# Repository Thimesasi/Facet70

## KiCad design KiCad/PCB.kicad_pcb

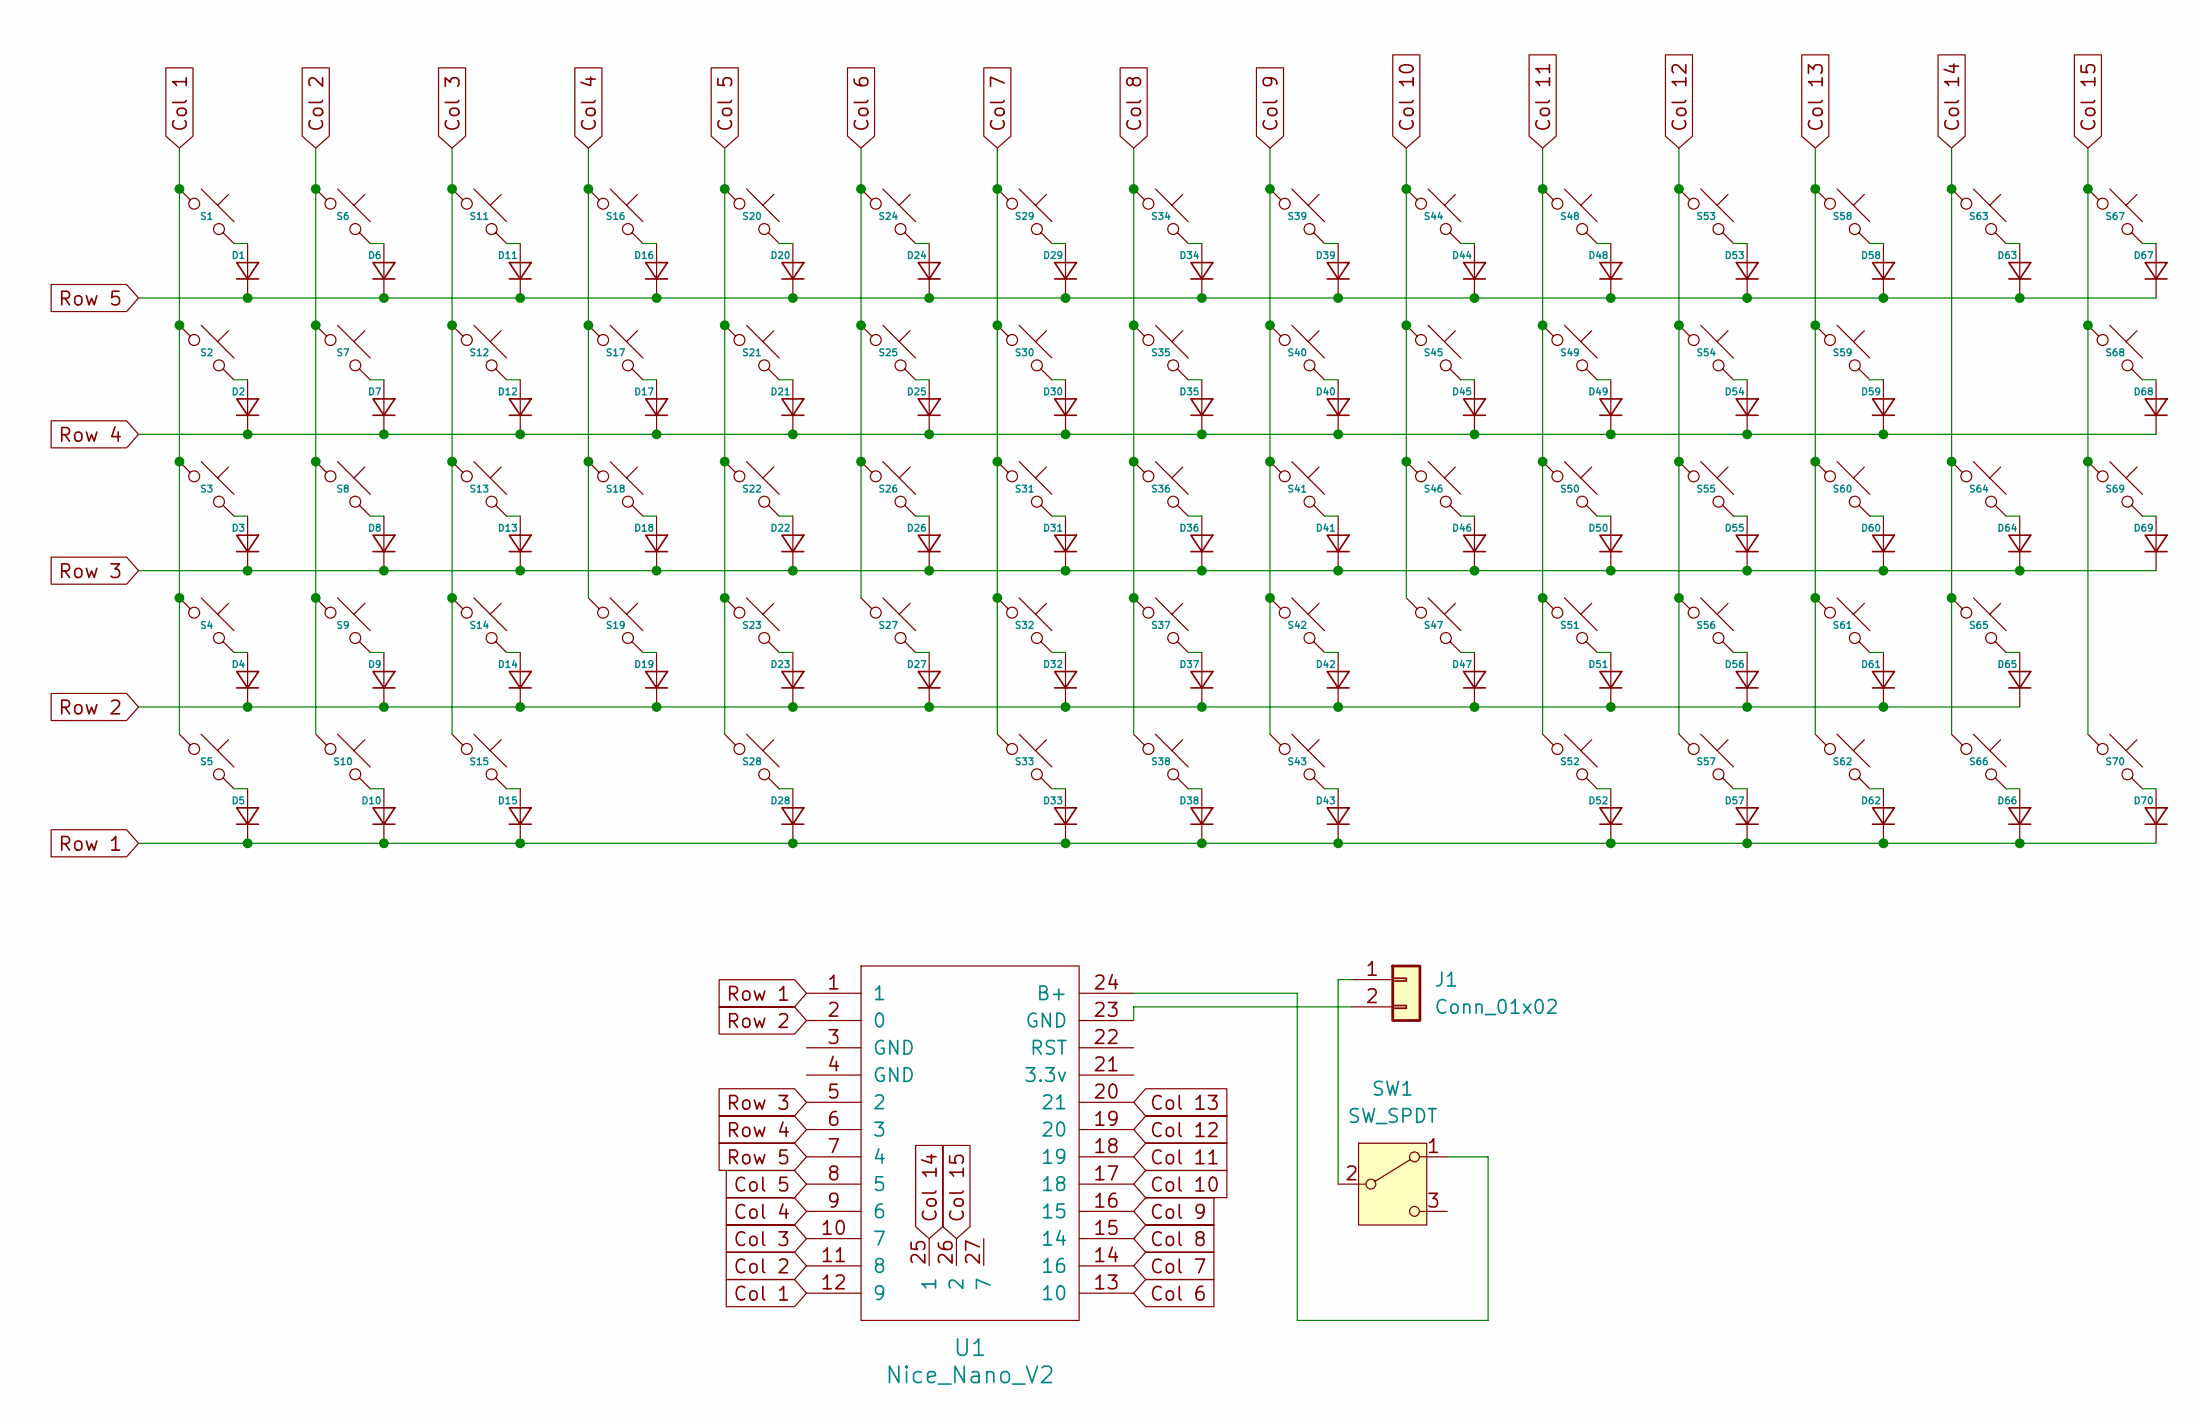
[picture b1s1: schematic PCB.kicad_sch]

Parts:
D1, D2, D3, D4, D5, D6, D7, D8, D9, D10, D11, D12, D13, D14, D15, D16, D17, D18, D19, D20, D21, D22, D23, D24, D25, D26, D27, D28, D29, D30, D31, D32, D33, D34, D35, D36, D37, D38, D39, D40, D41, D42, D43, D44, D45, D46, D47, D48, D49, D50, D51, D52, D53, D54, D55, D56, D57, D58, D59, D60, D61, D62, D63, D64, D65, D66, D67, D68, D69, D70: Diode_SOD-123
J1: Conn_01x02; JST_EH_S2B-EH_1x02_P2.50mm_Horizontal
S1, S2, S3, S4, S6, S7, S8, S9, S11, S12, S13, S14, S16, S17, S18, S19, S20, S21, S22, S23, S24, S25, S26, S27, S29, S30, S31, S32, S33, S34, S35, S36, S37, S38, S39, S40, S41, S42, S44, S45, S46, S47, S48, S49, S50, S51, S53, S54, S55, S56, S57, S58, S59, S60, S61, S62, S63, S64, S65, S66, S67, S70: Hotswap_MX_1.00u
S5, S10, S15: Hotswap_MX_1.25u
S28: Hotswap_MX_2.25u
S43, S52: Hotswap_MX_1.50u
S68: Hotswap_MX_2.00u
S69: Hotswap_MX_2.00u_90deg
SW1: SW_SPDT; SW_SPDT_PCM12
U1: Nice_Nano_V2

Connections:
Col 1: S1.1, S2.1, S3.1, S4.1, S5.1, U1.12 (9)
Col 2: S6.1, S7.1, S8.1, S9.1, S10.1, U1.11 (8)
Col 3: S11.1, S12.1, S13.1, S14.1, S15.1, U1.10 (7)
Col 4: S16.1, S17.1, S18.1, S19.1, U1.9 (6)
Col 5: S20.1, S21.1, S22.1, S23.1, S28.1, U1.8 (5)
Col 6: S24.1, S25.1, S26.1, S27.1, U1.13 (10)
Col 7: S29.1, S30.1, S31.1, S32.1, S33.1, U1.14 (16)
Col 8: S34.1, S35.1, S36.1, S37.1, S38.1, U1.15 (14)
Col 9: S39.1, S40.1, S41.1, S42.1, S43.1, U1.16 (15)
Col 10: S44.1, S45.1, S46.1, S47.1, U1.17 (18)
Col 11: S48.1, S49.1, S50.1, S51.1, S52.1, U1.18 (19)
Col 12: S53.1, S54.1, S55.1, S56.1, S57.1, U1.19 (20)
Col 13: S58.1, S59.1, S60.1, S61.1, S62.1, U1.20 (21)
Col 14: S63.1, S64.1, S65.1, S66.1, U1.25 (1)
Col 15: S67.1, S68.1, S69.1, S70.1, U1.26 (2)
unnamed: D1.2 (A), S1.2
unnamed: D2.2 (A), S2.2
unnamed: D3.2 (A), S3.2
unnamed: D4.2 (A), S4.2
unnamed: D5.2 (A), S5.2
unnamed: D6.2 (A), S6.2
unnamed: D7.2 (A), S7.2
unnamed: D8.2 (A), S8.2
unnamed: D9.2 (A), S9.2
unnamed: D10.2 (A), S10.2
unnamed: D11.2 (A), S11.2
unnamed: D12.2 (A), S12.2
unnamed: D13.2 (A), S13.2
unnamed: D14.2 (A), S14.2
unnamed: D15.2 (A), S15.2
unnamed: D16.2 (A), S16.2
unnamed: D17.2 (A), S17.2
unnamed: D18.2 (A), S18.2
unnamed: D19.2 (A), S19.2
unnamed: D20.2 (A), S20.2
unnamed: D21.2 (A), S21.2
unnamed: D22.2 (A), S22.2
unnamed: D23.2 (A), S23.2
unnamed: D24.2 (A), S24.2
unnamed: D25.2 (A), S25.2
unnamed: D26.2 (A), S26.2
unnamed: D27.2 (A), S27.2
unnamed: D28.2 (A), S28.2
unnamed: D29.2 (A), S29.2
unnamed: D30.2 (A), S30.2
unnamed: D31.2 (A), S31.2
unnamed: D32.2 (A), S32.2
unnamed: D33.2 (A), S33.2
unnamed: D34.2 (A), S34.2
unnamed: D35.2 (A), S35.2
unnamed: D36.2 (A), S36.2
unnamed: D37.2 (A), S37.2
unnamed: D38.2 (A), S38.2
unnamed: D39.2 (A), S39.2
unnamed: D40.2 (A), S40.2
unnamed: D41.2 (A), S41.2
unnamed: D42.2 (A), S42.2
unnamed: D43.2 (A), S43.2
unnamed: D44.2 (A), S44.2
unnamed: D45.2 (A), S45.2
unnamed: D46.2 (A), S46.2
unnamed: D47.2 (A), S47.2
unnamed: D48.2 (A), S48.2
unnamed: D49.2 (A), S49.2
unnamed: D50.2 (A), S50.2
unnamed: D51.2 (A), S51.2
unnamed: D52.2 (A), S52.2
unnamed: D53.2 (A), S53.2
unnamed: D54.2 (A), S54.2
unnamed: D55.2 (A), S55.2
unnamed: D56.2 (A), S56.2
unnamed: D57.2 (A), S57.2
unnamed: D58.2 (A), S58.2
unnamed: D59.2 (A), S59.2
unnamed: D60.2 (A), S60.2
unnamed: D61.2 (A), S61.2
unnamed: D62.2 (A), S62.2
unnamed: D63.2 (A), S63.2
unnamed: D64.2 (A), S64.2
unnamed: D65.2 (A), S65.2
unnamed: D66.2 (A), S66.2
unnamed: D67.2 (A), S67.2
unnamed: D68.2 (A), S68.2
unnamed: D69.2 (A), S69.2
unnamed: D70.2 (A), S70.2
unnamed: J1.1, SW1.2 (B)
unnamed: J1.2, U1.23 (GND)
unnamed: SW1.1 (A), U1.24 (B+)
Row 1: D5.1 (K), D10.1 (K), D15.1 (K), D28.1 (K), D33.1 (K), D38.1 (K), D43.1 (K), D52.1 (K), D57.1 (K), D62.1 (K), D66.1 (K), D70.1 (K), U1.1
Row 2: D4.1 (K), D9.1 (K), D14.1 (K), D19.1 (K), D23.1 (K), D27.1 (K), D32.1 (K), D37.1 (K), D42.1 (K), D47.1 (K), D51.1 (K), D56.1 (K), D61.1 (K), D65.1 (K), U1.2 (0)
Row 3: D3.1 (K), D8.1 (K), D13.1 (K), D18.1 (K), D22.1 (K), D26.1 (K), D31.1 (K), D36.1 (K), D41.1 (K), D46.1 (K), D50.1 (K), D55.1 (K), D60.1 (K), D64.1 (K), D69.1 (K), U1.5 (2)
Row 4: D2.1 (K), D7.1 (K), D12.1 (K), D17.1 (K), D21.1 (K), D25.1 (K), D30.1 (K), D35.1 (K), D40.1 (K), D45.1 (K), D49.1 (K), D54.1 (K), D59.1 (K), D68.1 (K), U1.6 (3)
Row 5: D1.1 (K), D6.1 (K), D11.1 (K), D16.1 (K), D20.1 (K), D24.1 (K), D29.1 (K), D34.1 (K), D39.1 (K), D44.1 (K), D48.1 (K), D53.1 (K), D58.1 (K), D63.1 (K), D67.1 (K), U1.7 (4)

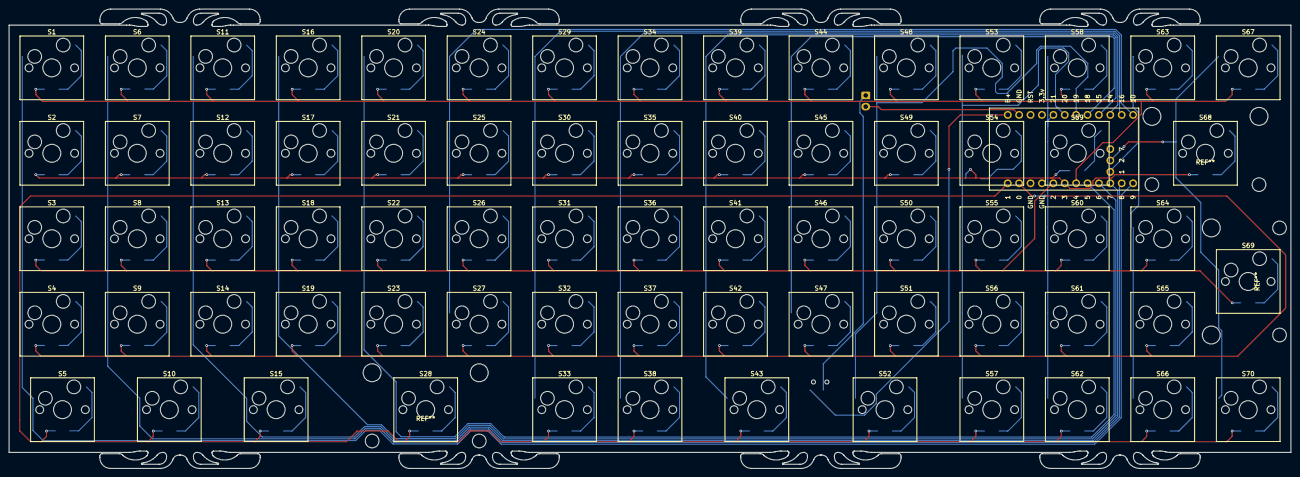
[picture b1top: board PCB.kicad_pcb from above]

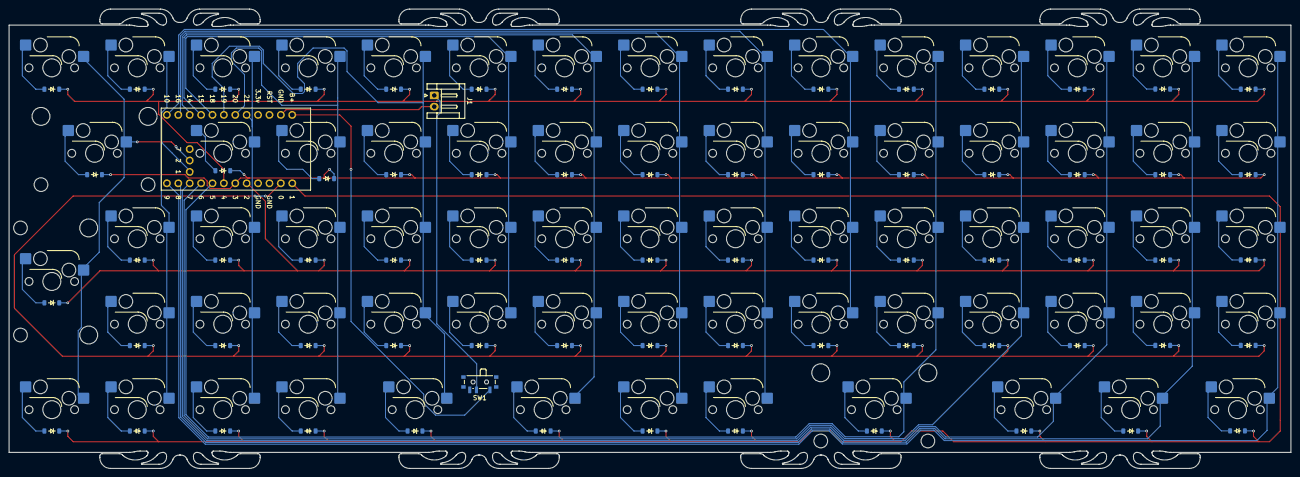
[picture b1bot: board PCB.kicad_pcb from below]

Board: 2 copper layers, 285.8 x 102.4 mm, 143 parts (72 on the bottom side), 93 nets.

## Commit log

2026-04-04 Update key layout data for keyboard mapping
2026-04-05 Create KiCad folder
2026-04-05 Add KiCad files
